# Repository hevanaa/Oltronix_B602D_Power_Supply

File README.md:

# Oltronix_B602D_Power_Supply

This repository contains a KiCAD PCB project of the original version A Oltronix regulator board in the LABPAC B602D and B603D power supply.

A repair description of the Power Supply is available here: https://baldpenguin.blogspot.com/2025/02/repairing-oltronix-b602d-power-supply.html

A cleaned up pdf version of the schematic is attached to this repository. Note that the pdf schematic contains an error: version B schematic has a short in opamp A30, input 5 and 6. 

Another discrepance is that in my version of the power supply B602D (version A), the diodes CR91-CR92 are connected like Version B schematic.

I've attached the version A and B schematics with the error fixed (the 0-30V and 0-60V jpg files).

Note that when creating the regulator board PCB with same dimensions as the original, extra long pin headers are required for clearance to some of the components on the main board. A modified version of the PCB would be better with a rounded/cut off corner on the side of the pin header connector.

---

## License

This repository contains a redesigned replacement for the regulator board used in the Oltronix power supply.

The original device and schematic are the property of their respective rights holders and are not included under this license.

This project covers only the original work created in this repository, including the PCB layout, modified schematic, BOM, and documentation.

This project is licensed under the CERN-OHL-S v2 (Strongly Reciprocal).

See `LICENSE` file for details.

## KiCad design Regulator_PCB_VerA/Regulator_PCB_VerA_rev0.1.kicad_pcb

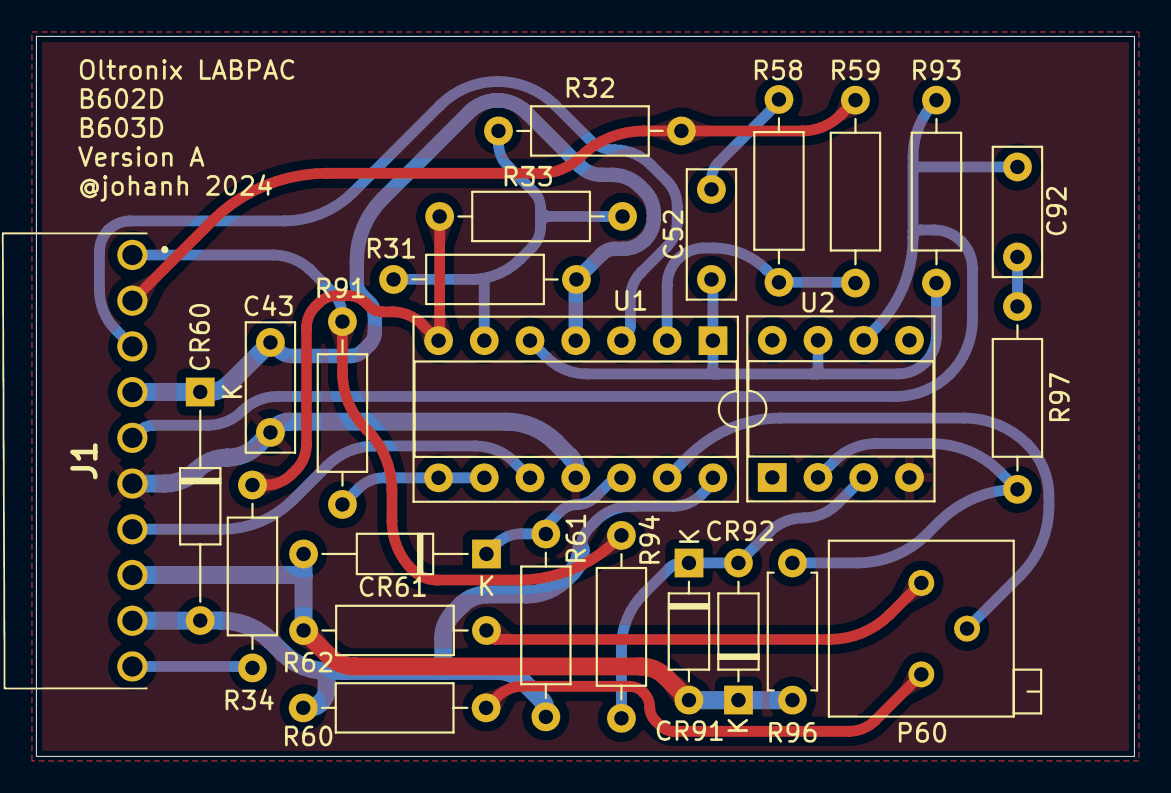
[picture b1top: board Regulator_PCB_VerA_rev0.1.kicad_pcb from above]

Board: 2 copper layers, 61.0 x 40.0 mm, 25 parts (0 on the bottom side), 23 nets.

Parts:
C43: 10p; C_Disc_D7.0mm_W2.5mm_P5.00mm
C52: 1n; C_Disc_D7.0mm_W2.5mm_P5.00mm
C92: 100pF; C_Disc_D7.0mm_W2.5mm_P5.00mm
CR60: ZF12; D_DO-35_SOD27_P12.70mm_Horizontal
CR61: 1N823; D_DO-35_SOD27_P10.16mm_Horizontal
CR91, CR92: IS921; D_DO-35_SOD27_P7.62mm_Horizontal
J1: Molex 22-16-2100; Molex_22-16-2100
P60: 1k; Potentiometer_Bourns_3296P_Horizontal
R31, R58, R97: 10k; R_Axial_DIN0207_L6.3mm_D2.5mm_P10.16mm_Horizontal
R32: 3.9k; R_Axial_DIN0207_L6.3mm_D2.5mm_P10.16mm_Horizontal
R33: 2.2M; R_Axial_DIN0207_L6.3mm_D2.5mm_P10.16mm_Horizontal
R34: 1.2k; R_Axial_DIN0207_L6.3mm_D2.5mm_P10.16mm_Horizontal
R59, R94: 1k; R_Axial_DIN0207_L6.3mm_D2.5mm_P10.16mm_Horizontal
R60: 1.8k 1%; R_Axial_DIN0207_L6.3mm_D2.5mm_P10.16mm_Horizontal
R61: 680 1%; R_Axial_DIN0207_L6.3mm_D2.5mm_P10.16mm_Horizontal
R62: 3.3k 1%; R_Axial_DIN0207_L6.3mm_D2.5mm_P10.16mm_Horizontal
R91: 2.7k 1%; R_Axial_DIN0207_L6.3mm_D2.5mm_P10.16mm_Horizontal
R93: 2.2k; R_Axial_DIN0207_L6.3mm_D2.5mm_P10.16mm_Horizontal
R96: 1k; R_Axial_DIN0207_L6.3mm_D2.5mm_P7.62mm_Horizontal
U1: MC3403P; DIP-14_W7.62mm_Socket
U2: LM741; DIP-8_W7.62mm_Socket

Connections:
/1: J1.1, R91.2, R94.2
/2: J1.2, R32.2, R59.2
/3: J1.3, U1.3 (+)
/4: C43.1, CR60.1 (K), J1.4, R31.1, U1.4 (V+)
/5: C92.1, J1.5, R93.2, U2.6
/6: C43.2, J1.6, U1.11 (V-), U2.4 (V-)
/7: J1.7, U1.10 (+)
/8: CR61.2 (A), CR91.2 (A), CR92.1 (K), J1.8, R62.2, R96.1
/9: CR60.2 (A), J1.9, R60.1, R61.1, U1.14
/10: J1.10, R34.2
unnamed: C52.2, R58.1
unnamed: C92.2, R97.1
unnamed: CR61.1 (K), R61.2, U1.12 (+)
unnamed: CR91.1 (K), CR92.2 (A), R94.1, U2.3 (+)
unnamed: P60.1, R60.2
unnamed: P60.3, R62.1
unnamed: R33.1, R34.1, U1.7
unnamed: R58.2, R59.1, U1.2 (-)
unnamed: C52.1, R93.1, U1.1, U1.5 (+), U2.7 (V+)
unnamed: R31.2, R32.1, R33.2, U1.6 (-)
unnamed: R91.1, U1.8, U1.9 (-)
unnamed: P60.2, U1.13 (-)
unnamed: R96.2, R97.2, U2.2 (-)

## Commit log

2025-02-22 Added schematics and user manual
2025-02-22 Added VerA regulator
2025-02-22 Picture of the original regulator board and a KiCAD rendering
2025-03-08 Corrected page size and fixed errors in schematic B
2026-06-27 Create LICENSE
